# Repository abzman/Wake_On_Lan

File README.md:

Wake_On_Lan
===========

the documents to accompany a project in converting a pci-network card into a network attaced bit

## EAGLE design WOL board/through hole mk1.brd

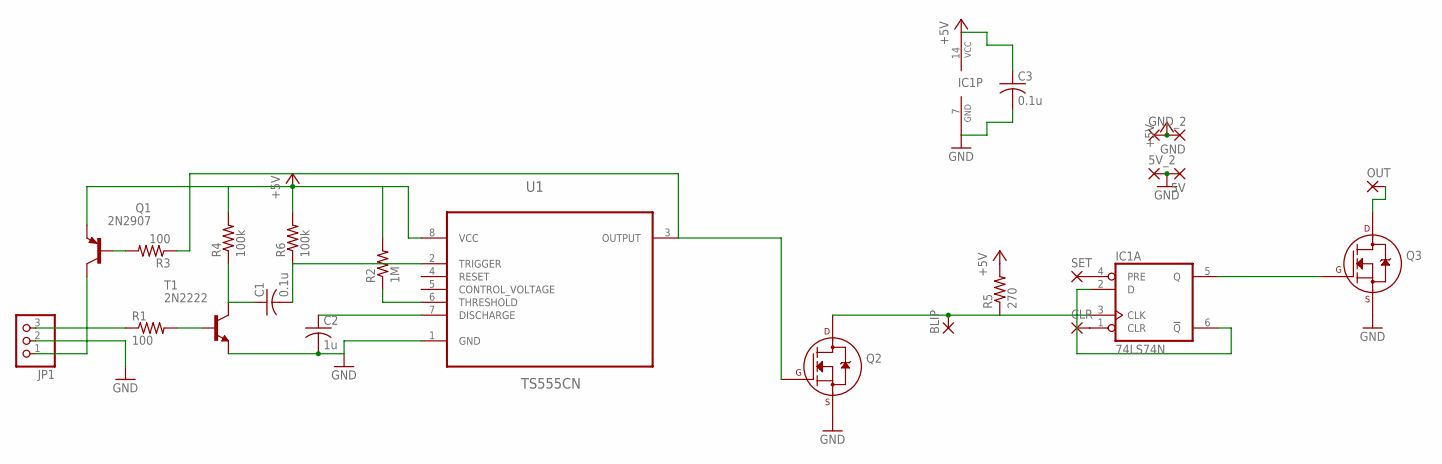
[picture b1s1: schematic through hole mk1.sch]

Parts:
5V, 5V_2: 1,6/0,8
BLIP: 1,6/0,8
C1, C3: 0.1u; C025-030X050
C2: 1u; C025-030X050
CLR: 1,6/0,8
GND: 1,6/0,8
GND_2: 1,6/0,8
IC1: 74LS74N; DIL14
JP1: PINHD-1X3; 1X03
OUT: 1,6/0,8
Q1: 2N2907; TO92-EBC-OVAL
Q2, Q3: 2N7000_TO92; TO-92
R1, R3: 100; 0204/5
R2: 1M; 0204/5
R4, R6: 100k; 0204/5
R5: 270; 0204/5
SET: 1,6/0,8
T1: 2N2222; TO92-EBC-OVAL
U1: TS555CN; DIP254P762X533-8

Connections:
+5V: C3.1, GND.1, GND_2.1, IC1.14 (VCC), Q1.E, R2.2, R4.2, R5.2, R6.2, U1.8 (VCC)
GND: 5V.1, 5V_2.1, C2.2, C3.2, IC1.7 (GND), JP1.2, Q2.1 (S), Q3.1 (S), T1.E, U1.1 (GND)
unnamed: Q1.B, R3.2
unnamed: JP1.1, Q1.C
unnamed: R1.2, T1.B
unnamed: JP1.3, R1.1
unnamed: IC1.4 (PRE), SET.1
unnamed: C1.1, R4.1, T1.C
unnamed: C1.2, R6.1, U1.2 (TRIGGER)
unnamed: CLR.1, IC1.1 (CLR)
unnamed: R2.1, U1.6 (THRESHOLD)
unnamed: Q2.2 (G), R3.1, U1.3 (OUTPUT)
unnamed: BLIP.1, IC1.3 (CLK), Q2.3 (D), R5.1
unnamed: IC1.2 (D), IC1.6 (!Q)
unnamed: IC1.5 (Q), Q3.2 (G)
unnamed: C2.1, U1.7 (DISCHARGE)
unnamed: OUT.1, Q3.3 (D)

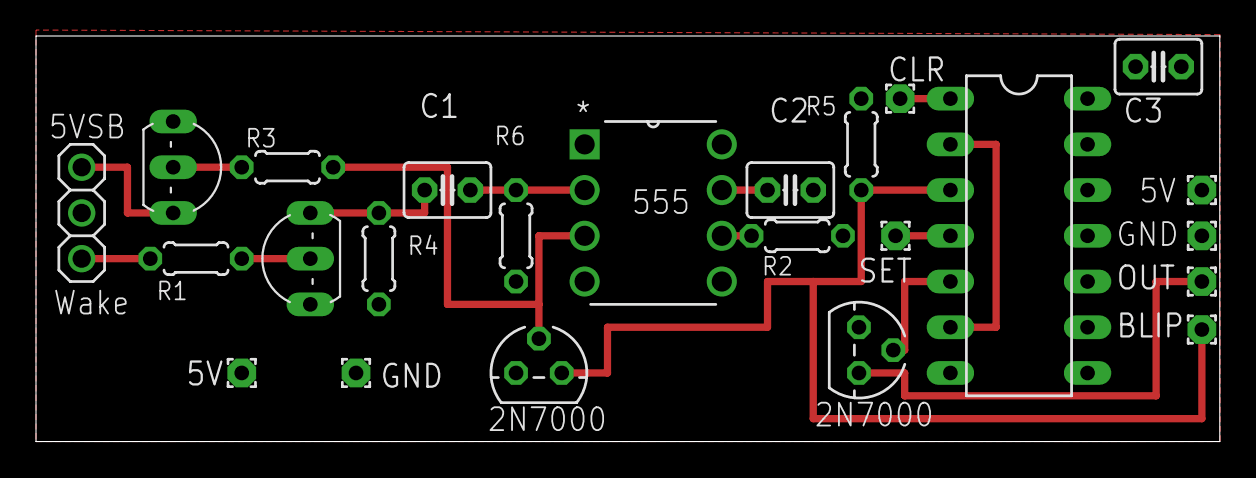
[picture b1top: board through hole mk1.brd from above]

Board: 2 copper layers, 65.8 x 22.5 mm, 24 parts (0 on the bottom side), 17 nets.

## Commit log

2014-01-24 added through-hole board
2014-01-25 added image
